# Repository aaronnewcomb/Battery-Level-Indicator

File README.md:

# Battery-Level-Indicator
Simple circuit for detecting when LiPo batteries drop below a certain level

# What is it?
A small circuit that uses an Attiny 13A microcontroller to measure the voltage of a 3.7V LiPo battery and sends a signal to another device when the voltage gets to a certain level.

# Theory of operation
The Attiny is supplied by a steady 5V (important for voltage reference). One of the ADCs measures the voltage level of the battery. When the voltage drops below a certain level, the Attiny will set another pin high. This signal goes through a voltage divider to lower it from 5V to 3.3V for compliance with 3.3V tolerant IO pins. This way you can tell another device like a Raspberry Pi that the battery is low and you should shut the device down either manually or programatically. The battery leval at which the signal is triggered can be adjusted with the potentiometer on the board or in the Arduino program that runs on the Attiny. The program should work on any pin compatible version of the Attiny (i.e. Attiny25, 85, etc).

This is especially useful when using a cheap battery charger that doesn't have this functionality built in like this one.
https://www.ebay.com/itm/Lithium-Li-ion-18650-3-7V-4-2V-Battery-Charger-Board-DC-DC-Step-Up-Boost-Module/232791040584?ssPageName=STRK%3AMEBIDX%3AIT&_trksid=p2057872.m2749.l2649

You can also buy more robust charging circuits that are slightly more expensive and include a low battery indication like this one from Adafruit.
https://www.adafruit.com/product/2465

You could also use this board as a easy way to program 8 pin Attiny's without having to use a breadboard.

# Programming
Program the Attiny13 with an Arduino Uno. 

https://create.arduino.cc/projecthub/taunoerik/programming-attiny13-with-arduino-uno-07beba

Program the Attiny 25,45,85 with an Arduino Uno.

https://create.arduino.cc/projecthub/arjun/programming-attiny85-with-arduino-uno-afb829

I have labeled the pins on the board with the Uno pins they should be connected to.

# Usage
More coming soon

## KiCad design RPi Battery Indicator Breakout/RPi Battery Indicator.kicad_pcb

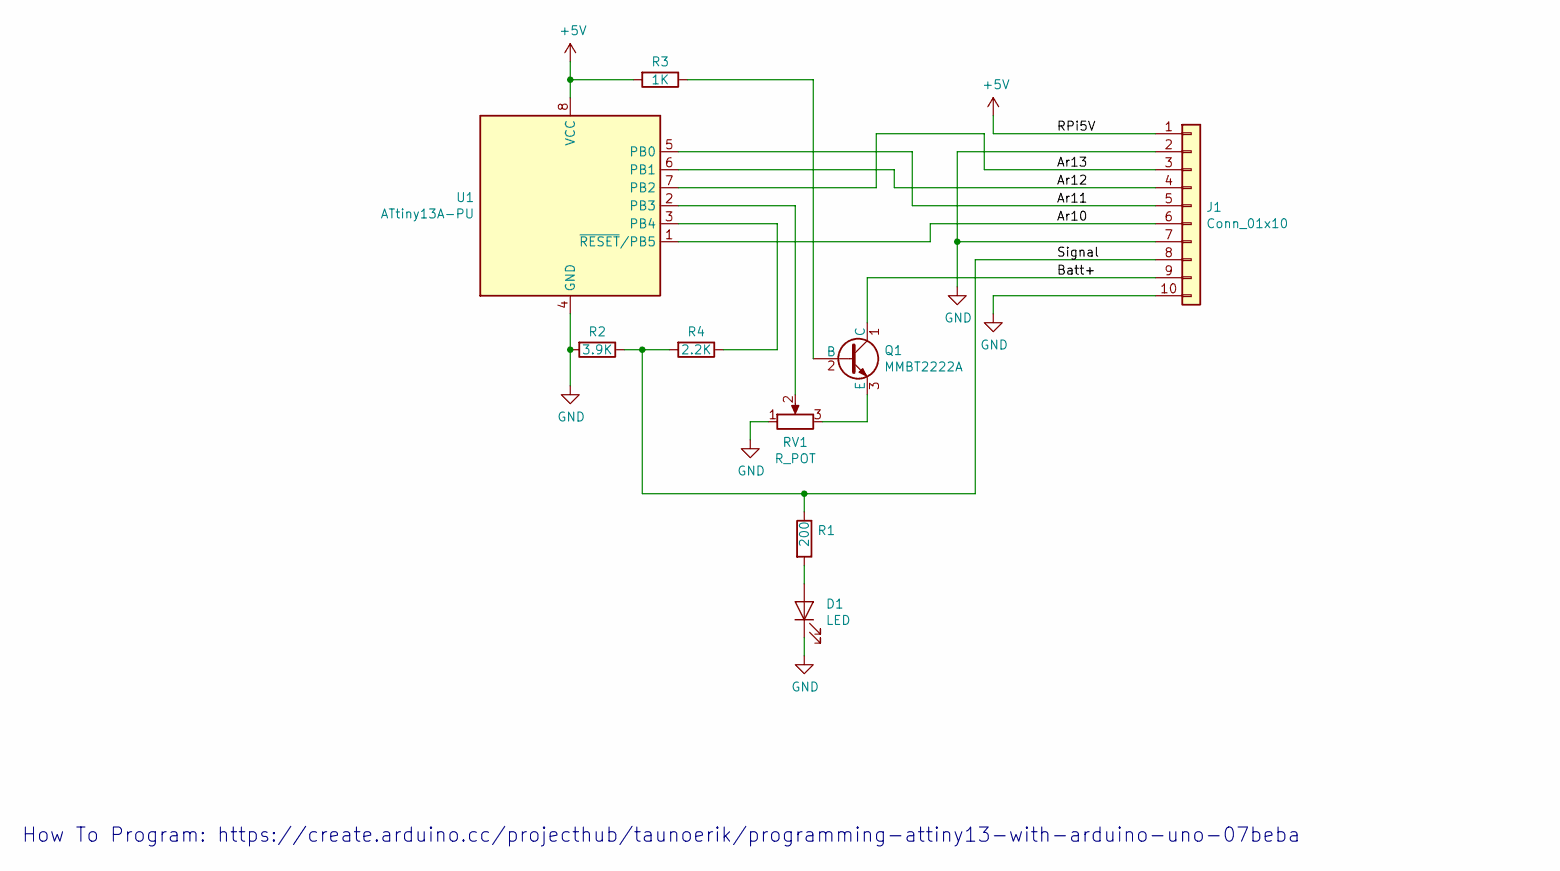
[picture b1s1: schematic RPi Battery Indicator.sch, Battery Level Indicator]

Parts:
D1: LED; LED_0805_2012Metric
J1: Conn_01x10; PinHeader_1x10_P2.54mm_Vertical
Q1: MMBT2222A; TO-92
R1: 200; R_0805_2012Metric
R2: 3.9K; R_0805_2012Metric
R3: 1K; R_0805_2012Metric
R4: 2.2K; R_0805_2012Metric
RV1: R_POT; Trimpot_3.8mmx3.6mm_TC33X-2-103E
U1: ATtiny13A-PU; DIP-8_W7.62mm

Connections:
+5V: J1.1, R3.2, U1.8 (VCC)
/Ar10: J1.6, U1.1 (~RESET~/PB5)
/Ar11: J1.5, U1.5 (PB0)
/Ar12: J1.4, U1.6 (PB1)
/Ar13: J1.3, U1.7 (PB2)
/Batt+: J1.9, Q1.1 (C)
/Signal: J1.8, R1.1, R2.1, R4.2
GND: D1.1 (K), J1.2, J1.7, J1.10, R2.2, RV1.1, U1.4 (GND)
unnamed: D1.2 (A), R1.2
unnamed: Q1.2 (B), R3.1
unnamed: Q1.3 (E), RV1.3
unnamed: R4.1, U1.3 (PB4)
unnamed: RV1.2, U1.2 (PB3)

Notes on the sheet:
How To Program: https://create.arduino.cc/projecthub/taunoerik/programming-attiny13-with-arduino-uno-07beba

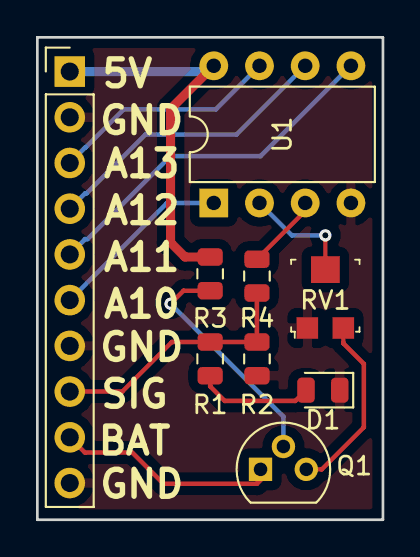
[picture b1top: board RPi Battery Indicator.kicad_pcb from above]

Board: 2 copper layers, 19.2 x 26.8 mm, 9 parts (0 on the bottom side), 13 nets.

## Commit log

2019-09-02 Initial file upload
2019-09-02 Changed ADC values to allow for lower voltage detection
